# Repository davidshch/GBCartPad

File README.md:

# GBCartPad 👾
A 16-key Game Boy Cartridge Macropad with an OLED display and RGB LEDs for each key that uses KMK firmware!

## Why'd I make it
I've always wanted to make a full-stack hardware project and design my own PCB, so this was my first introduction to that. I also love Nintendo and thought the Game Boy cartridge design would make a really nice case for something like a macropad. I'll probably use it for basic things, such as a numpad for my laptop and some shortcuts I use, but the important part for me is that it's built and working. It was a great learning experience overall, and it will definitely help me with future hardware projects I want to make.

## BOM
- XIAO RP2040
- 16x 1N4148 Diodes
- 0.91in OLED Display
- 16x SK6812 RGB LEDs
- 16x Cherry MX Switches
- 5x M3x16 Bolt
- 5x M3 Heatset
- 16x Blank DSA Keycaps

## CAD Model

Made in Fusion360!

## Schematic

## PCB

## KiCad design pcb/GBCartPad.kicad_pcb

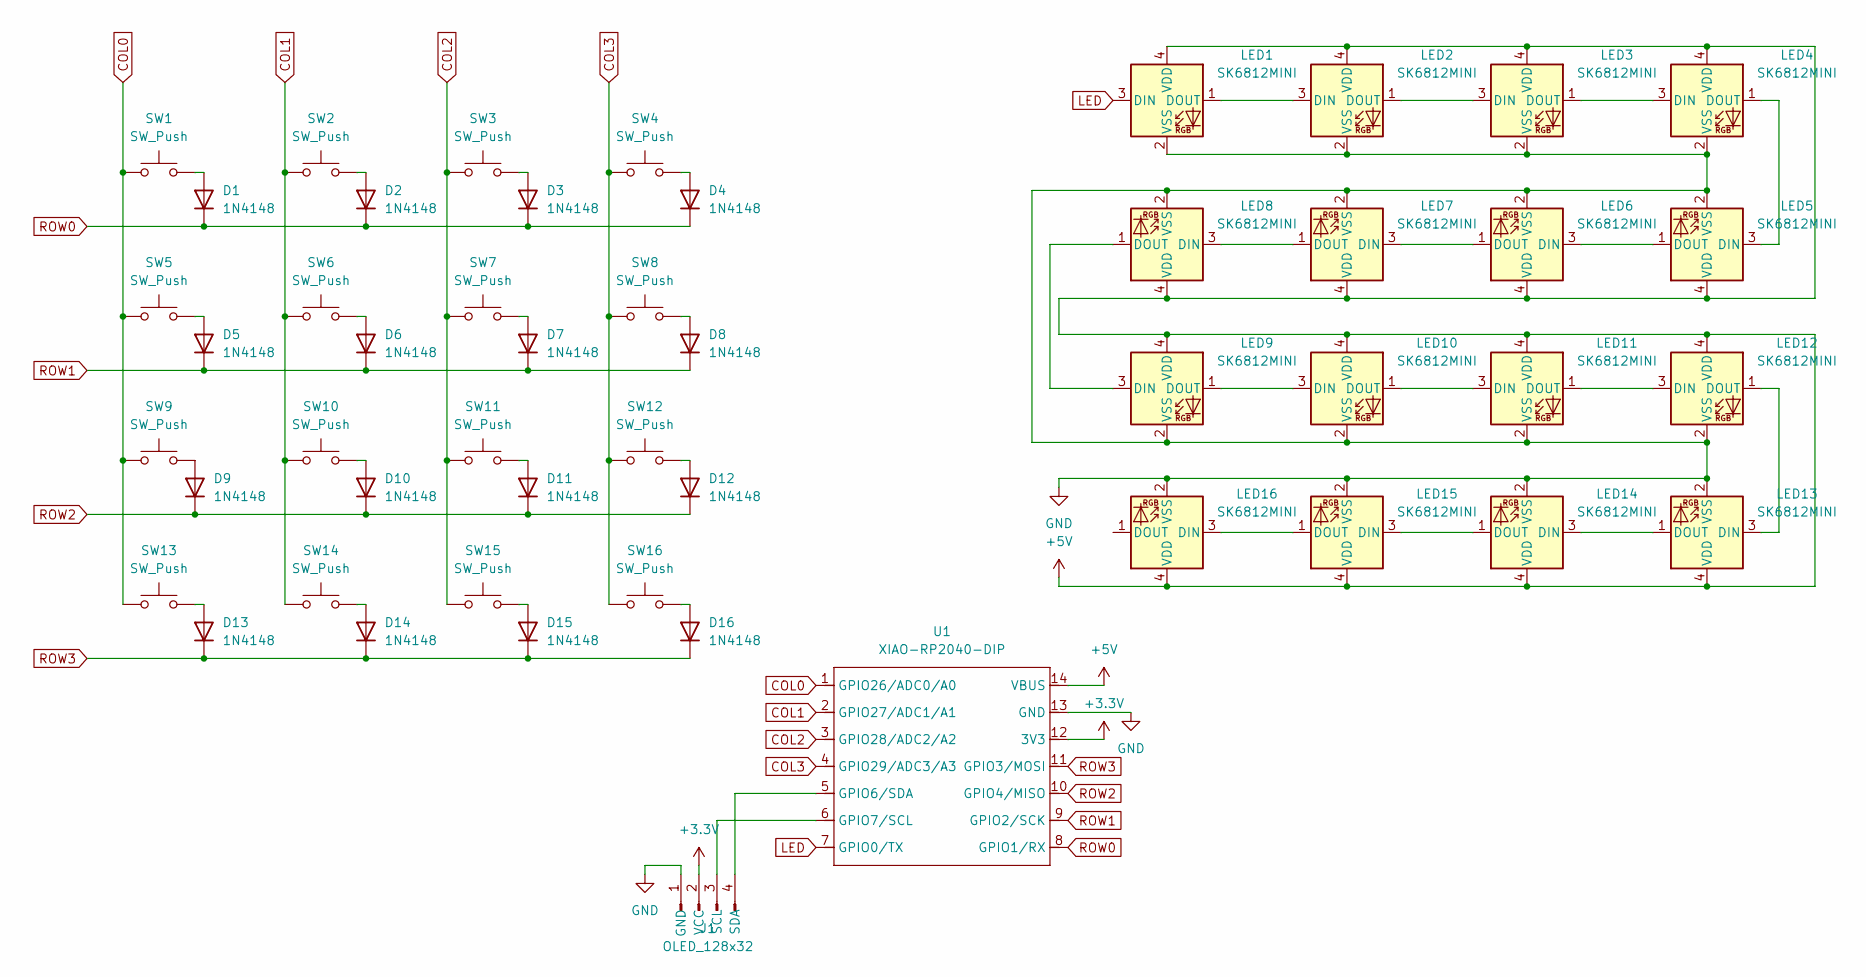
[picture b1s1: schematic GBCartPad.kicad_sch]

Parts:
D1, D2, D3, D4, D5, D6, D7, D8, D9, D10, D11, D12, D13, D14, D15, D16: 1N4148; D_DO-35_SOD27_P7.62mm_Horizontal
J1: OLED_128x32; SSD1306-0.91-OLED-4pin-128x32
LED1, LED2, LED3, LED4, LED5, LED6, LED7, LED8, LED9, LED10, LED11, LED12, LED13, LED14, LED15, LED16: SK6812MINI; LED_SK6812MINI
SW1, SW2, SW3, SW4, SW5, SW6, SW7, SW8, SW9, SW10, SW11, SW12, SW13, SW14, SW15, SW16: SW_Push; SW_Cherry_MX_PCB_1.00u
U1: XIAO-RP2040-DIP

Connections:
+3.3V: J1.2 (VCC), U1.12 (3V3)
+5V: LED1.4 (VDD), LED2.4 (VDD), LED3.4 (VDD), LED4.4 (VDD), LED5.4 (VDD), LED6.4 (VDD), LED7.4 (VDD), LED8.4 (VDD), LED9.4 (VDD), LED10.4 (VDD), LED11.4 (VDD), LED12.4 (VDD), LED13.4 (VDD), LED14.4 (VDD), LED15.4 (VDD), LED16.4 (VDD), U1.14 (VBUS)
COL0: SW1.1, SW5.1, SW9.1, SW13.1, U1.1 (GPIO26/ADC0/A0)
COL1: SW2.1, SW6.1, SW10.1, SW14.1, U1.2 (GPIO27/ADC1/A1)
COL2: SW3.1, SW7.1, SW11.1, SW15.1, U1.3 (GPIO28/ADC2/A2)
COL3: SW4.1, SW8.1, SW12.1, SW16.1, U1.4 (GPIO29/ADC3/A3)
GND: J1.1 (GND), LED1.2 (VSS), LED2.2 (VSS), LED3.2 (VSS), LED4.2 (VSS), LED5.2 (VSS), LED6.2 (VSS), LED7.2 (VSS), LED8.2 (VSS), LED9.2 (VSS), LED10.2 (VSS), LED11.2 (VSS), LED12.2 (VSS), LED13.2 (VSS), LED14.2 (VSS), LED15.2 (VSS), LED16.2 (VSS), U1.13 (GND)
LED: LED1.3 (DIN), U1.7 (GPIO0/TX)
unnamed: D1.2 (A), SW1.2
unnamed: D2.2 (A), SW2.2
unnamed: D3.2 (A), SW3.2
unnamed: D4.2 (A), SW4.2
unnamed: D5.2 (A), SW5.2
unnamed: D6.2 (A), SW6.2
unnamed: D7.2 (A), SW7.2
unnamed: D8.2 (A), SW8.2
unnamed: D9.2 (A), SW9.2
unnamed: D10.2 (A), SW10.2
unnamed: D11.2 (A), SW11.2
unnamed: D12.2 (A), SW12.2
unnamed: D13.2 (A), SW13.2
unnamed: D14.2 (A), SW14.2
unnamed: D15.2 (A), SW15.2
unnamed: D16.2 (A), SW16.2
unnamed: J1.3 (SCL), U1.6 (GPIO7/SCL)
unnamed: J1.4 (SDA), U1.5 (GPIO6/SDA)
unnamed: LED1.1 (DOUT), LED2.3 (DIN)
unnamed: LED2.1 (DOUT), LED3.3 (DIN)
unnamed: LED3.1 (DOUT), LED4.3 (DIN)
unnamed: LED4.1 (DOUT), LED5.3 (DIN)
unnamed: LED5.1 (DOUT), LED6.3 (DIN)
unnamed: LED6.1 (DOUT), LED7.3 (DIN)
unnamed: LED7.1 (DOUT), LED8.3 (DIN)
unnamed: LED8.1 (DOUT), LED9.3 (DIN)
unnamed: LED9.1 (DOUT), LED10.3 (DIN)
unnamed: LED10.1 (DOUT), LED11.3 (DIN)
unnamed: LED11.1 (DOUT), LED12.3 (DIN)
unnamed: LED12.1 (DOUT), LED13.3 (DIN)
unnamed: LED13.1 (DOUT), LED14.3 (DIN)
unnamed: LED14.1 (DOUT), LED15.3 (DIN)
unnamed: LED15.1 (DOUT), LED16.3 (DIN)
ROW0: D1.1 (K), D2.1 (K), D3.1 (K), D4.1 (K), U1.8 (GPIO1/RX)
ROW1: D5.1 (K), D6.1 (K), D7.1 (K), D8.1 (K), U1.9 (GPIO2/SCK)
ROW2: D9.1 (K), D10.1 (K), D11.1 (K), D12.1 (K), U1.10 (GPIO4/MISO)
ROW3: D13.1 (K), D14.1 (K), D15.1 (K), D16.1 (K), U1.11 (GPIO3/MOSI)

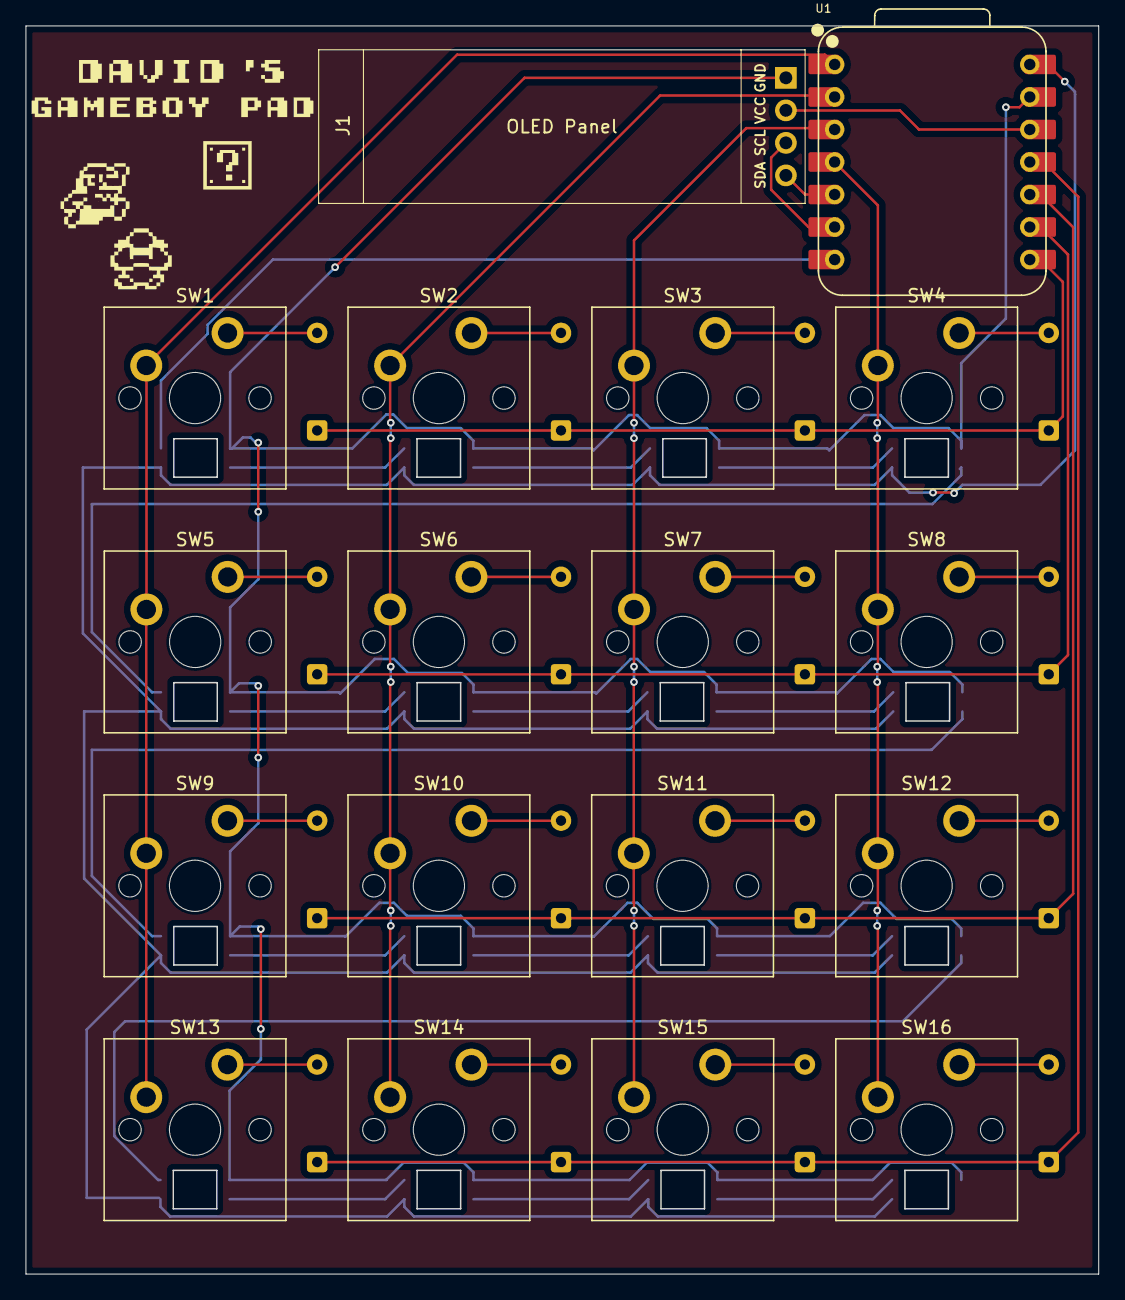
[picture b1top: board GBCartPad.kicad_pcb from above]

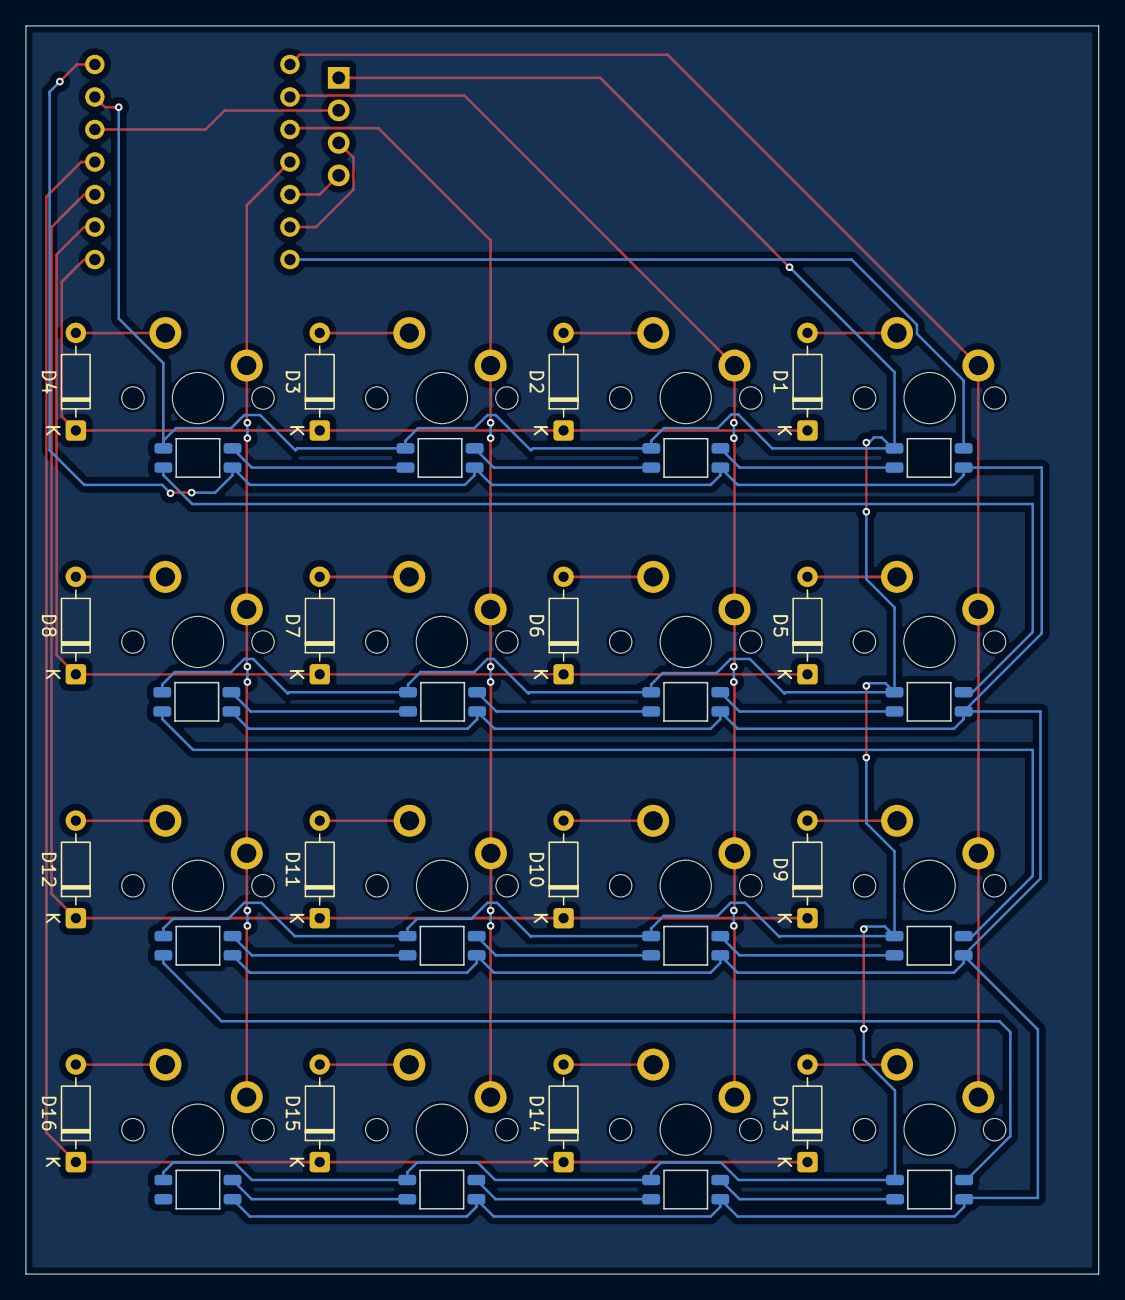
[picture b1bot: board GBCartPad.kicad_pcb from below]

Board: 2 copper layers, 83.8 x 97.5 mm, 50 parts (32 on the bottom side), 45 nets.

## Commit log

2025-07-08 Add project files
